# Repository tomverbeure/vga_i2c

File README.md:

# VGA I2C GPIO + Atari 2600 Joystick Extender

**A detailed write-up about this project can be found [here](https://tomverbeure.github.io/2019/02/05/VGA-I2C-My-First-PCB.html).**

The [Pano Logic G1](https://github.com/tomverbeure/panologic) doesn't have an easy
way to add GPIOs or non-USB input devices.

If you want to control a game like PacMan with a joystick, you need to be creative.
One way to do that is by soldering some wires to connect unused VGA pins to the
FPGA as demonstrated by the [Pano Man](https://github.com/skiphansen/pano_man) project.

But only allow for a lot of buttons. The Pano Man README suggested connecting a
GPIO I2C expander to the I2C wires of the VGA cable.

This project does exactly that!

It's a VGA to VGA feedthru board that taps the I2C wires, adds an I2C GPIO expander, connects it
to 2 Atari 2600 joystick ports, 4 additional switches and 2 LEDs.

I shared the schematics of this board with Skip, the author of Pano Man, and he made a
version that supports this board!

The design is very simple and it was the perfect project to learn KiCAD and design and 
send out for production my first PCB.

The schematic:

The PCB layout:

The result:

[Video](https://player.vimeo.com/video/315809161)

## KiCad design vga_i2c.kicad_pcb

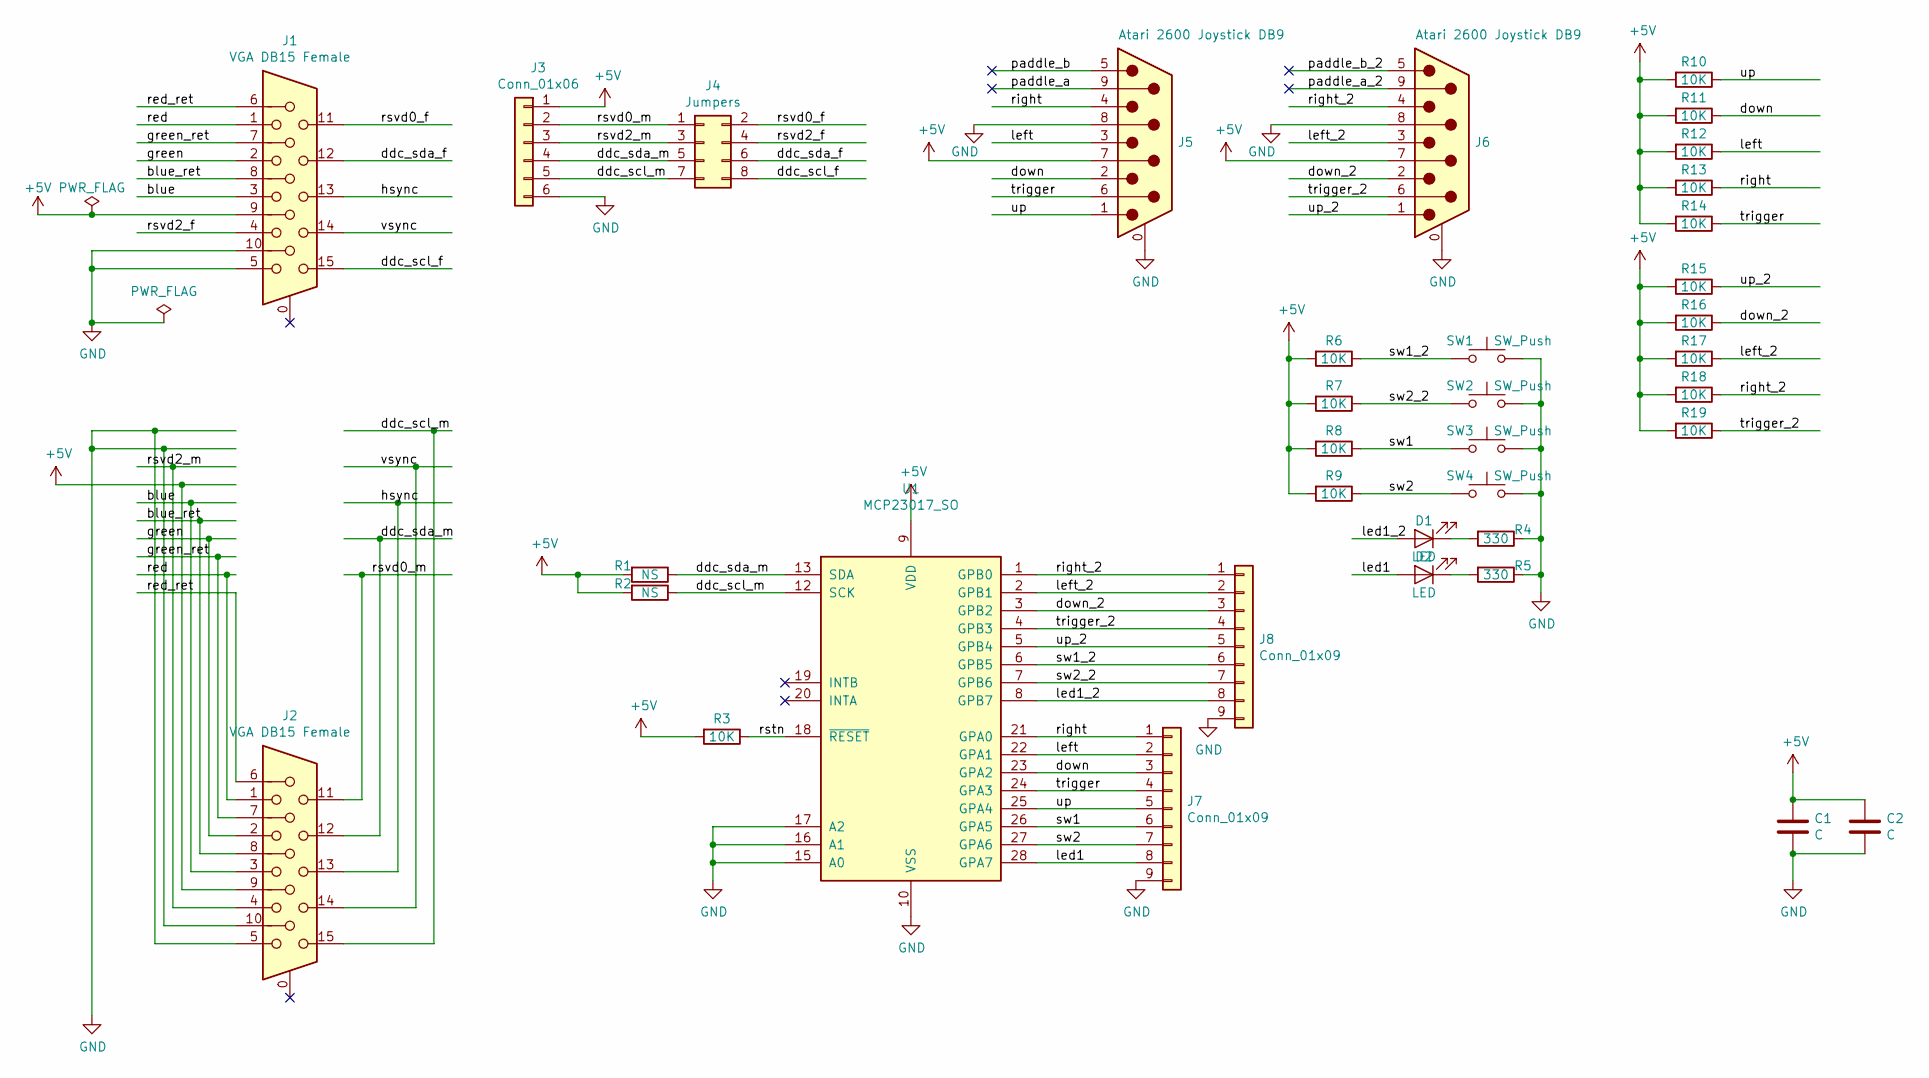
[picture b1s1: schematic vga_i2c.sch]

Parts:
C1, C2: C; C_0603_HandSoldering
D1, D2: LED; LED_0805_HandSoldering
J1, J2: VGA DB15 Female; NORCOMP_181-015-213R561
J3: Conn_01x06; Pin_Header_Straight_1x06_Pitch2.54mm
J4: Jumpers; Pin_Header_Straight_2x04_Pitch2.54mm
J5, J6: Atari 2600 Joystick DB9; TE_1-1634580-2
J7, J8: Conn_01x09; Pin_Header_Straight_1x09_Pitch2.54mm
R1, R2: NS; R_0603_HandSoldering
R3, R6, R7, R8, R9, R10, R11, R12, R13, R14, R15, R16, R17, R18, R19: 10K; R_0603_HandSoldering
R4, R5: 330; R_0603_HandSoldering
SW1, SW2, SW3, SW4: SW_Push; SW_PUSH_6mm
U1: MCP23017_SO; SOIC-28W_7.5x18.7mm_Pitch1.27mm

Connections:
+5V: C1.1, C2.1, J1.9, J2.9, J3.1, J5.7, J6.7, R1.2, R2.2, R3.2, R6.2, R7.2, R8.2, R9.2, R10.2, R11.2, R12.2, R13.2, R14.2, R15.2, R16.2, R17.2, R18.2, R19.2, U1.9 (VDD)
/blue: J1.3, J2.3
/blue_ret: J1.8, J2.8
/ddc_scl_f: J1.15, J4.8
/ddc_scl_m: J2.15, J3.5, J4.7, R2.1, U1.12 (SCK)
/ddc_sda_f: J1.12, J4.6
/ddc_sda_m: J2.12, J3.4, J4.5, R1.1, U1.13 (SDA)
/down: J5.2, J7.3, R11.1, U1.23 (GPA2)
/down_2: J6.2, J8.3, R16.1, U1.3 (GPB2)
/green: J1.2, J2.2
/green_ret: J1.7, J2.7
/hsync: J1.13, J2.13
/led1: D2.2 (A), J7.8, U1.28 (GPA7)
/led1_2: D1.2 (A), J8.8, U1.8 (GPB7)
/left: J5.3, J7.2, R12.1, U1.22 (GPA1)
/left_2: J6.3, J8.2, R17.1, U1.2 (GPB1)
/paddle_a: J5.9
/paddle_a_2: J6.9
/paddle_b: J5.5
/paddle_b_2: J6.5
/red: J1.1, J2.1
/red_ret: J1.6, J2.6
/right: J5.4, J7.1, R13.1, U1.21 (GPA0)
/right_2: J6.4, J8.1, R18.1, U1.1 (GPB0)
/rstn: R3.1, U1.18 (~RESET~)
/rsvd0_f: J1.11, J4.2
/rsvd0_m: J2.11, J3.2, J4.1
/rsvd2_f: J1.4, J4.4
/rsvd2_m: J2.4, J3.3, J4.3
/sw1: J7.6, R8.1, SW3.1, U1.26 (GPA5)
/sw1_2: J8.6, R6.1, SW1.1, U1.6 (GPB5)
/sw2: J7.7, R9.1, SW4.1, U1.27 (GPA6)
/sw2_2: J8.7, R7.1, SW2.1, U1.7 (GPB6)
/trigger: J5.6, J7.4, R14.1, U1.24 (GPA3)
/trigger_2: J6.6, J8.4, R19.1, U1.4 (GPB3)
/up: J5.1, J7.5, R10.1, U1.25 (GPA4)
/up_2: J6.1, J8.5, R15.1, U1.5 (GPB4)
/vsync: J1.14, J2.14
GND: C1.2, C2.2, J1.5, J1.10, J2.5, J2.10, J3.6, J5.0 (PAD), J5.8, J6.0 (PAD), J6.8, J7.9, J8.9, R4.1, R5.1, SW1.2, SW2.2, SW3.2, SW4.2, U1.10 (VSS), U1.15 (A0), U1.16 (A1), U1.17 (A2)
unnamed: D1.1 (K), R4.2
unnamed: D2.1 (K), R5.2

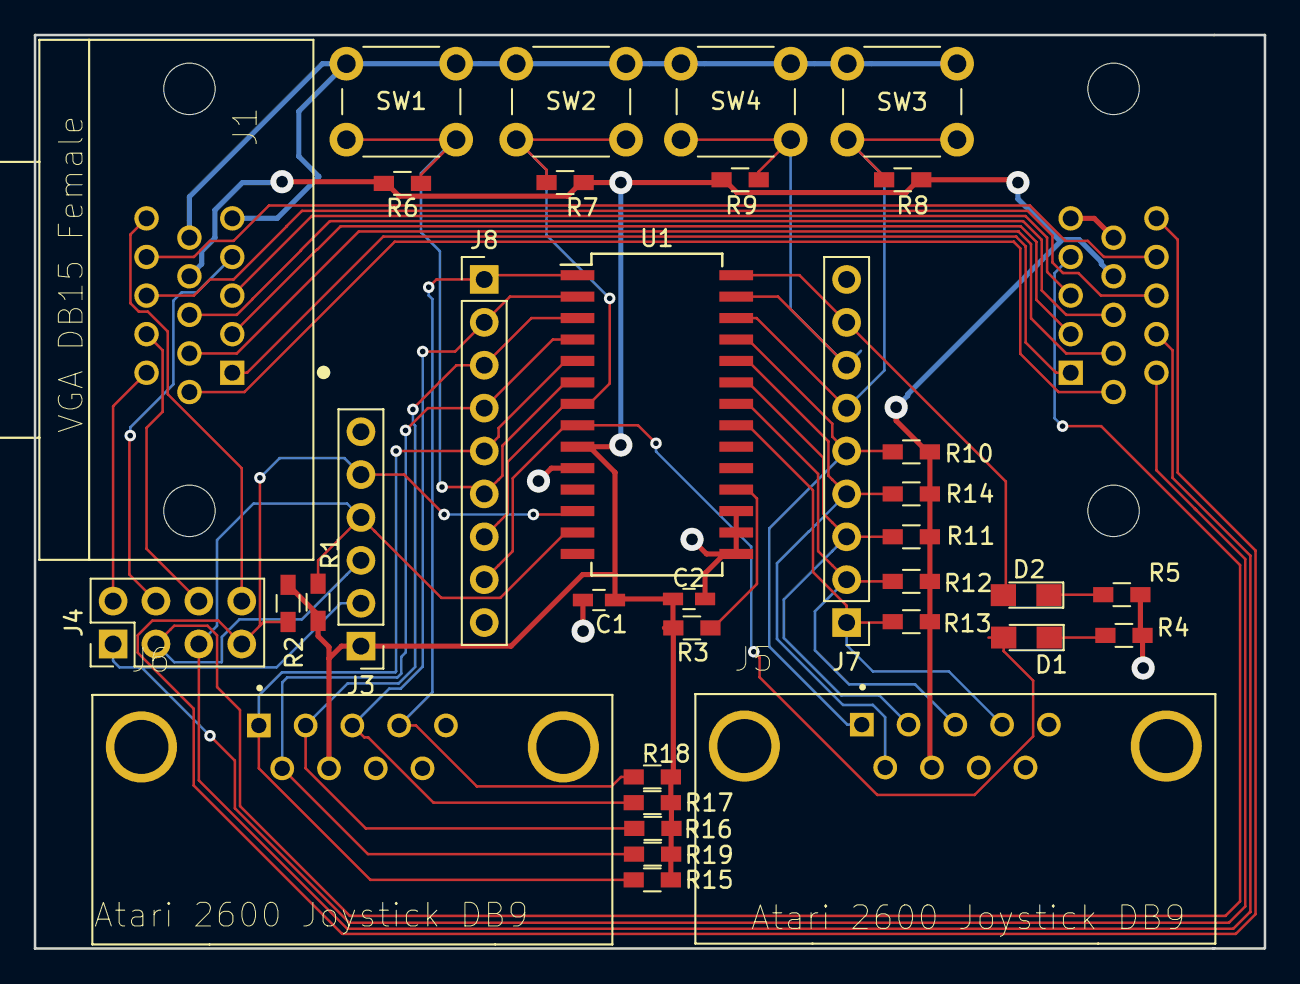
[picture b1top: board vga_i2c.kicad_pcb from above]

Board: 2 copper layers, 72.8 x 54.1 mm, 36 parts (1 on the bottom side), 37 nets.

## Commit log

2019-01-09 Schematic rev 1 ready.
2019-01-10 Version 1
2019-01-10 !st production version.
2019-01-10 PDF of schematic and pcb
2019-01-11 Version with 2 joysticks.
2019-01-11 pdf files.
2019-02-07 Pictures.
2019-02-07 Crop images.
2019-02-07 Link to Video
2019-02-07 Link to video.
